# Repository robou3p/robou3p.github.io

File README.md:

# RoboU3P (robou3p.github.io)

V projektu RoboU3P je bil razvit robotski sistem za izobraževanje treh generacij mladine: osnovnošolcev, srednješolcev in študentov, namenjen prenosu znanja med generacijami.

Projekt sofinancirata Republika Slovenija in Evropska unija iz Evropskega socialnega sklada v okviru razpisa Študentski inovativni projekti za družbeno korist 2016–2018 Javnega štipendijskega, razvojnega, invalidskega in preživninskega sklada Republike Slovenije.

[Evropski socialni sklad](http://ec.europa.eu/esf/home.jsp?langId=sl) 

[Ministrstvo za izobraževanje, znanost in šport](http://www.mizs.gov.si) 

[Fakulteta za strojništvo, Univerza v Ljubljani](http://fs.uni-lj.si) 

# Repozitorij

[Repozitorij projekta RoboU3P](https://github.com/robou3p/robou3p.github.io/)

## Struktura repozitorija

- *Android aplikacija*: Izvorna koda Android aplikacije.
- *Ardublockly - Scratch okolje*: Programsko okolje za programiranje v jeziku Scratch.
- *Arduino knjižnica*: Knjižnica za programsko okolje Arduino.
- *Naloge za robota*: Učne vsebine in učne priprave, ostalo pedagoško gradivo.
- *Ostalo*: Ostale, podporne datoteke.
- *Wiki_images*: Slike, ki se uporabljajo v Wiki-ju.

## ⭐ Wiki stran

Vsa potrebna dokumentacija - navodila za namestitev, opis funkcij robota, ipd. je na voljo na Wikiju.

Povezava: 👉 [https://github.com/robou3p/robou3p.github.io/wiki](https://github.com/robou3p/robou3p.github.io/wiki) 👈

## Prenos knjižnice

Knjižnico za robota za Arduino lahko prenesete neposredno v ZIP datoteki v [*Releases* razdelku](https://github.com/robou3p/robou3p.github.io/releases).

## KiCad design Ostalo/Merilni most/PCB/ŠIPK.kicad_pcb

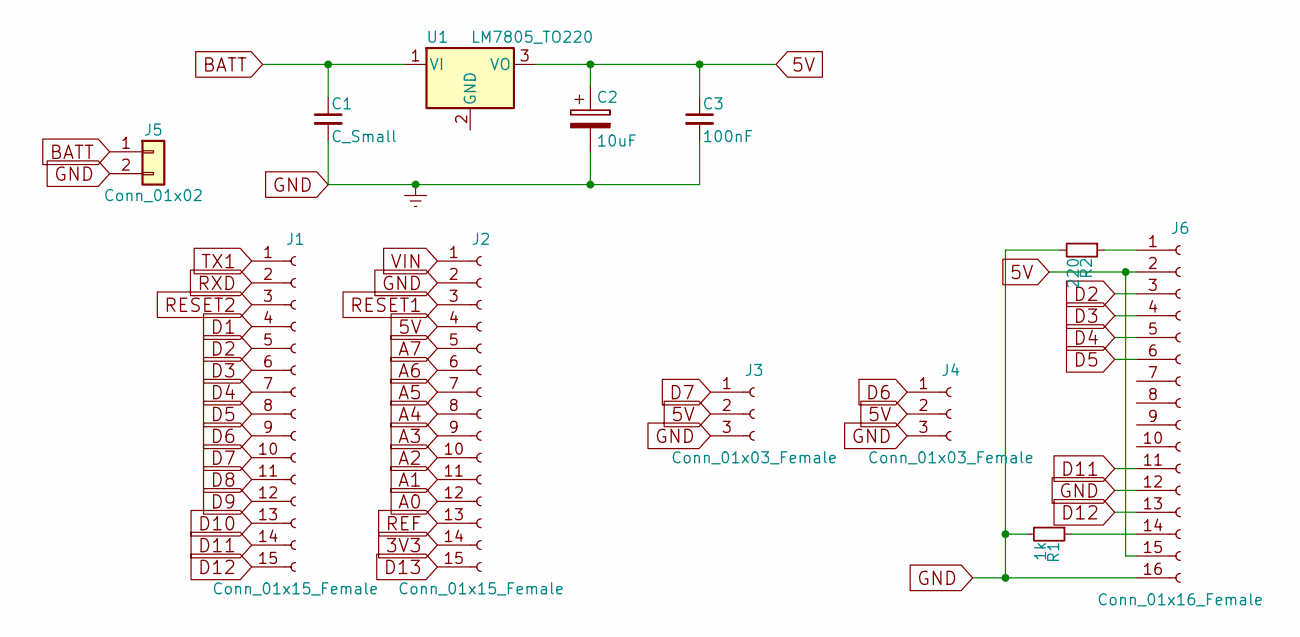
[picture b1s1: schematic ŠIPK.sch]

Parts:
C1: C_Small; CP_Radial_D10.0mm_P5.00mm
C2: 10uF; CP_Tantalum_Case-R_EIA-2012-12_Reflow
C3: 100nF; C_0805
J1, J2: Conn_01x15_Female; Socket_Strip_Straight_1x15_Pitch2.54mm
J3, J4: Conn_01x03_Female; Socket_Strip_Straight_1x03_Pitch2.54mm
J5: Conn_01x02; Pin_Header_Straight_2x01_Pitch2.54mm
J6: Conn_01x16_Female; Socket_Strip_Straight_1x16_Pitch2.54mm
R1: 1k; R_0805
R2: 220; R_0805
U1: LM7805_TO220; TO-252-3_TabPin2

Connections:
3V3: J2.14
5V: C2.1, C3.1, J2.4, J3.2, J4.2, J6.2, J6.15, U1.3 (VO)
A0: J2.12
A1: J2.11
A2: J2.10
A3: J2.9
A4: J2.8
A5: J2.7
A6: J2.6
A7: J2.5
BATT: C1.1, J5.1, U1.1 (VI)
D1: J1.4
D2: J1.5, J6.3
D3: J1.6, J6.4
D4: J1.7, J6.5
D5: J1.8, J6.6
D6: J1.9, J4.1
D7: J1.10, J3.1
D8: J1.11
D9: J1.12
D10: J1.13
D11: J1.14, J6.11
D12: J1.15, J6.13
D13: J2.15
GND: C1.2, C2.2, C3.2, J2.2, J3.3, J4.3, J5.2, J6.12, J6.16, R1.2, R2.2
unnamed: J6.1, R2.1
unnamed: J6.14, R1.1
REF: J2.13
RESET1: J2.3
RESET2: J1.3
RXD: J1.2
TX1: J1.1
VIN: J2.1

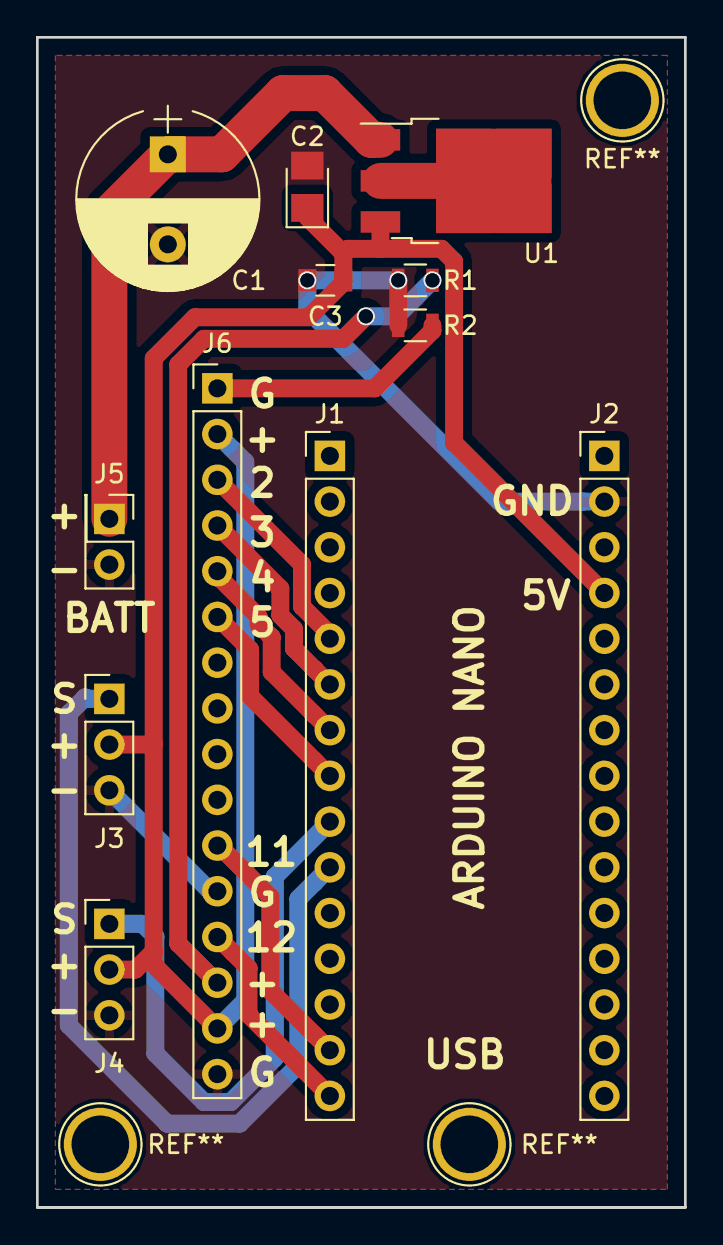
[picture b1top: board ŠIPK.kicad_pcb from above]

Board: 2 copper layers, 36.0 x 65.0 mm, 12 parts (0 on the bottom side), 13 nets.

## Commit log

2018-02-20 Dodana Android aplikacija
2018-02-20 Dodana knjižnica robota in Scratch navodila
2018-02-20 Dodana .zip knjižnica
2018-02-23 Uspešen build aplikacije v Android Studio 3
2018-03-03 Dodana navodila za Git
2018-03-03 Posodobljena verzija navodil
2018-03-03 Primer brisanja navodil
2018-03-05 Primer, kako bi lahko izgledala aplikacija
2018-03-10 Dodana lib Test
2018-03-13 Popravki - gumbi, kalibracija
2018-03-16 test lib change
2018-03-16 Arduino koda
2018-03-16 Naloge za tehniški dan in seznam funkcij, ki jih je potrebno napisati.
2018-03-16 Odstanil gumb za kalibracijo in opcijo premaknil v meni Naslovna vrstica aplikacije sedaj prikazuje status povezave (not connected, connecting, connected to)
    Splošna ureditev obstoječe kode v več razredov (ampak mislim, da jih je enako kot prej, lol)
    TODO: reimplementiraj kalibracijo
2018-03-18 ActivityMain -> MainActivity Implemented calibration dialog
2018-03-18 update test distance
2018-03-18 Added test output to main activity (to be replaced with something better) Added SensorConfigurationLoader that saves and loads sensor calibration vectors (no need to calibrate every time app is run)
2018-03-20 osnutek učne priprave, prva učna priprava.
2018-03-24 distance test 002
2018-03-25 test_distance002
2018-03-30 Petkovi osnutki učnih priprav za tehniški dan za osnovnošilce
2018-04-01 new test lib
2018-04-01 EEPROM functions
2018-04-02 Create images
2018-04-02 Popravki, compassView
2018-04-03 napaka 001
2018-04-07 Joystick update (WIP)
2018-04-07 Updated Android Studio to 3.1, gradle version update
2018-04-07 Removed submodule Bugstick android library
2018-04-07 readded Bugstick android library
2018-04-14 accel + gyro
2018-04-16 That's a cool commit you got there. I’ve got a buddy who’s an expert in this and I’d like to have him take a look at it, so I know what I'm dealing with.
2018-04-16 Dodan dokument o napredku aplikacije
2018-04-18 20180418 mk
2018-04-24 in app help; prevodi; testni build apk
2018-04-24 Added arduino code used with android app
2018-04-24 Removed old app apk
2018-04-24 read all 12 saved values
2018-04-24 koncni testni program Arduino IDE
2018-04-24 added volatile
2018-04-24 odstranil 3 knjiznjice
2018-04-24 odstranil vse glede IMU
2018-05-07 Prevod, popravki.
2018-05-08 uporaba fukncije BEEP in IF stavek
2018-05-09 dodana premra koles
2018-05-09 dodani preračuni za hitrost
2018-05-09 spremenjen koeficient za enkoderje
2018-05-10 Add files via upload
    Uporaba fukncije BEEP -pomoč pri sestavi blokcev
2018-05-12 spremenjen motor, distance in line
2018-05-12 dodajanje komentarjev in lepsi izpis
2018-05-12 spremembe casovnih konstant
2018-05-13 Fixed sending data when using sensor; Fixed searching for new bluetooth devices (requires location permission)
2018-05-13 Display "not connected" if other bluetooth device disconnected
2018-05-13 apk release build v1.0.1
2018-05-14 Dodana navodila za namestitev Android aplikacije
2018-05-14 spremenjen delay() v robot.go() in robot.turn() za boljšo zanesljivost
2018-05-15 zadnji delay spremenjen
2018-05-15 delay spremenjen
2018-05-15 android.ino fixed parameters
2018-05-15 Končna verzija (možni še popravki)
2018-05-15 Natančen potek
2018-05-15 Učna enota - natančen potek
2018-05-21 temp
2018-05-21 indent popravljen
2018-05-21 coments and order
2018-05-21 slike sestavni deli
2018-05-21 obrezano
2018-05-21 variable name changed
2018-05-22 Create Ardublockly
2018-05-22 komentarji
2018-05-22 added ardublockly
2018-05-22 debugging
2018-05-22 Končni učni pripravi za 1. in 2. uro.
2018-05-24 Create Končne učne priprave
2018-05-25 Struktura repozitorija
2018-05-25 Added boards.js, python...
2018-05-25 added ardublockly appdata to gitignore
2018-05-25 Added missing ardublockly repository files
2018-05-25 optimizacija prostora
2018-05-25 Spremembe ardublockly
2018-05-25 Create Merilni sistem
2018-05-25 Create Merilni most
2018-05-25 nov folder
2018-05-25 lib arduino
2018-05-25 debug
2018-05-27 pobrisani odvecni fajli
2018-05-28 calibrate 10s
2018-05-28 delete
